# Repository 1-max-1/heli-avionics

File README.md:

# heli-avionics
This repository contains the electronics and software for a rc-helicopter control system. This includes an onboard flight computer and a mobile application for remote control.
The PCB is designed to drive coaxial blades using brushed DC motors. It also contains an rf transciever chip for wireless communication and a pressure sensor for altitude measurement.

I had to learn alot for this project, as there were several things I had no experience with such as the radio transceiver circuitry. In the end, it turned out well and was very fun to make.

# PCBWay
The PCB fabrication and assembly was sponsored by [PCBWay](https://www.pcbway.com/). I’m pleased with how it turned out, and I’ve written a short review below based on my experience working with them.

#### PCB Quality
The boards appear durable and well-made, with solid electrical connectivity. Silkscreen print is sharp and the overall finish gives off a professional feel.

#### Assembly Quality
Assembly was just as good. All components were placed with precision and the soldering was clean. There were no bridges, no excess, and everything stayed neatly within the boundaries.

#### Communication & Support
Working with PCBWay was a smooth experience. They were professional and quick to respond to any questions I had. One thing I really appreciated was their communication before making any key decisions. For example:
- When a part was unavailable, they suggested alternatives instead of just swapping it.
- They double-checked with me before sourcing alternative components.
- After assembly, the team contacted me about the orientation of a particular component as the markings were slightly ambiguous.

#### Pricing & Turnaround
Pricing was fair, considering the quality and the support included. Quoting and sourcing components was made easy — PCBWay handled that for me, which saved a lot of time. Shipping was fast and the boards arrived well-packed.

Overall, I'm happy with the result and wouldn’t hesitate to use PCBWay again in future projects. If you’re looking for a PCB manufacturer that’s reliable, responsive, and produces high-quality results, they’re worth checking out.

# Electronics
**Motor drivers**

The system uses three `DRV8212` BDC motor drivers to drive the tail and coaxial propellors. Some analysis shows that these chips should handle the current demands while remaining below maximum safe temperatures.
The motor driver circuit also includes significant bulk capacitance to handle large spikes in motor current.

The first design of the motor driver circuit used 1 driver chip for both motors. However after more testing, I found that the motors drew more current than expected when at full power. This was over the maximum limit of the motor driver chip. Initially, I started looking for replacement chips with better capabilities. However, the options were either too big, unavailable or could not operate at the voltage I wanted. Eventually, I realised this was the wrong way to go about it and decided to have another look at the original drivers. I discovered that if the 2 outputs on the chip were joined together, this would effectively double the maximum current, which was now sufficient for these motors. However, this solution does require 2 driver chips instead of one. I initially had concerns about space on the board, but after many hours of rearranging and rerouting I found a way to fit both parts on the board.

**MCU**

The MCU is an `atmega4808`. Although possibly not the fanciest choice, I selected this one because it's easy to program, I have used it before, and I know how to make it work.

**Programming**

The MCU can be programmed through UPDI or through the USART pins (once the bootloader has been uploaded). These are broken out to pin headers for easy access. The board also includes an external reset line + button.

I have also broken out an I2C line and a spare GPIO to another pin header in case I want to add more things onto the helicopter in the future.

**Radio**

This board includes a rf transceiver: `nrf24l01`. Like the MCU, this is not fancy but there's alot of documentation for it and I'd rather start with something easier because my rf knowledge is limited (for now).
The board contains an impedance matching network to match the transceiver output to 50 ohms. A wire antenna is used because it should give the best range and I dont have space for a PCB antenna or any bulky connectors like SMA. The antenna will also have to be tuned by cutting it to a specific length. I think UC has network analyzers which could help with this...

**Power regulation**

There are two seperate `TPS7A2030` voltage regulators - one for the radio and one for the rest of the circuit. This is done to try and minimize noise on the radio. The MCU also keeps track of the battery voltage through a divider to ensure that it remains at a safe level.

**Sensors**

The board includes a `BMP390` pressure sensor which can be used to determine the altitude of the helicopter.

# Software
TODO

Using platformIO, c++

### AeroLink
IN PROGRESS

This is a small esp32-based device which is placed near the user when flying the helicopter.
It acts as a bridge between the flight computer and the mobile application.
BLE messages are processed and sent over a long range nrf24 link, and vice versa.

# Controller app
IN PROGRESS

This is a [React Native](https://reactnative.dev/) mobile application for control of the helicopter.
It includes throttle and directional controls, trim adjustment, buttons for extra features (e.g. auto landing), telemetry display and signal strength indication.
The app automatically connects to the AeroLink and communicates with it.

# Why?
I found this helicopter in an e-waste center. The remote was missing and some of the electronics seemed to be burnt. 

|  | 
|:--:| 
| *Disassembled helicopter on test stand* |

After taking it apart and relubricating all the shafts and gears, I tested the motors and they still seemed to work fine.
I decided it would be fun to fix it up and make my own controller for it.

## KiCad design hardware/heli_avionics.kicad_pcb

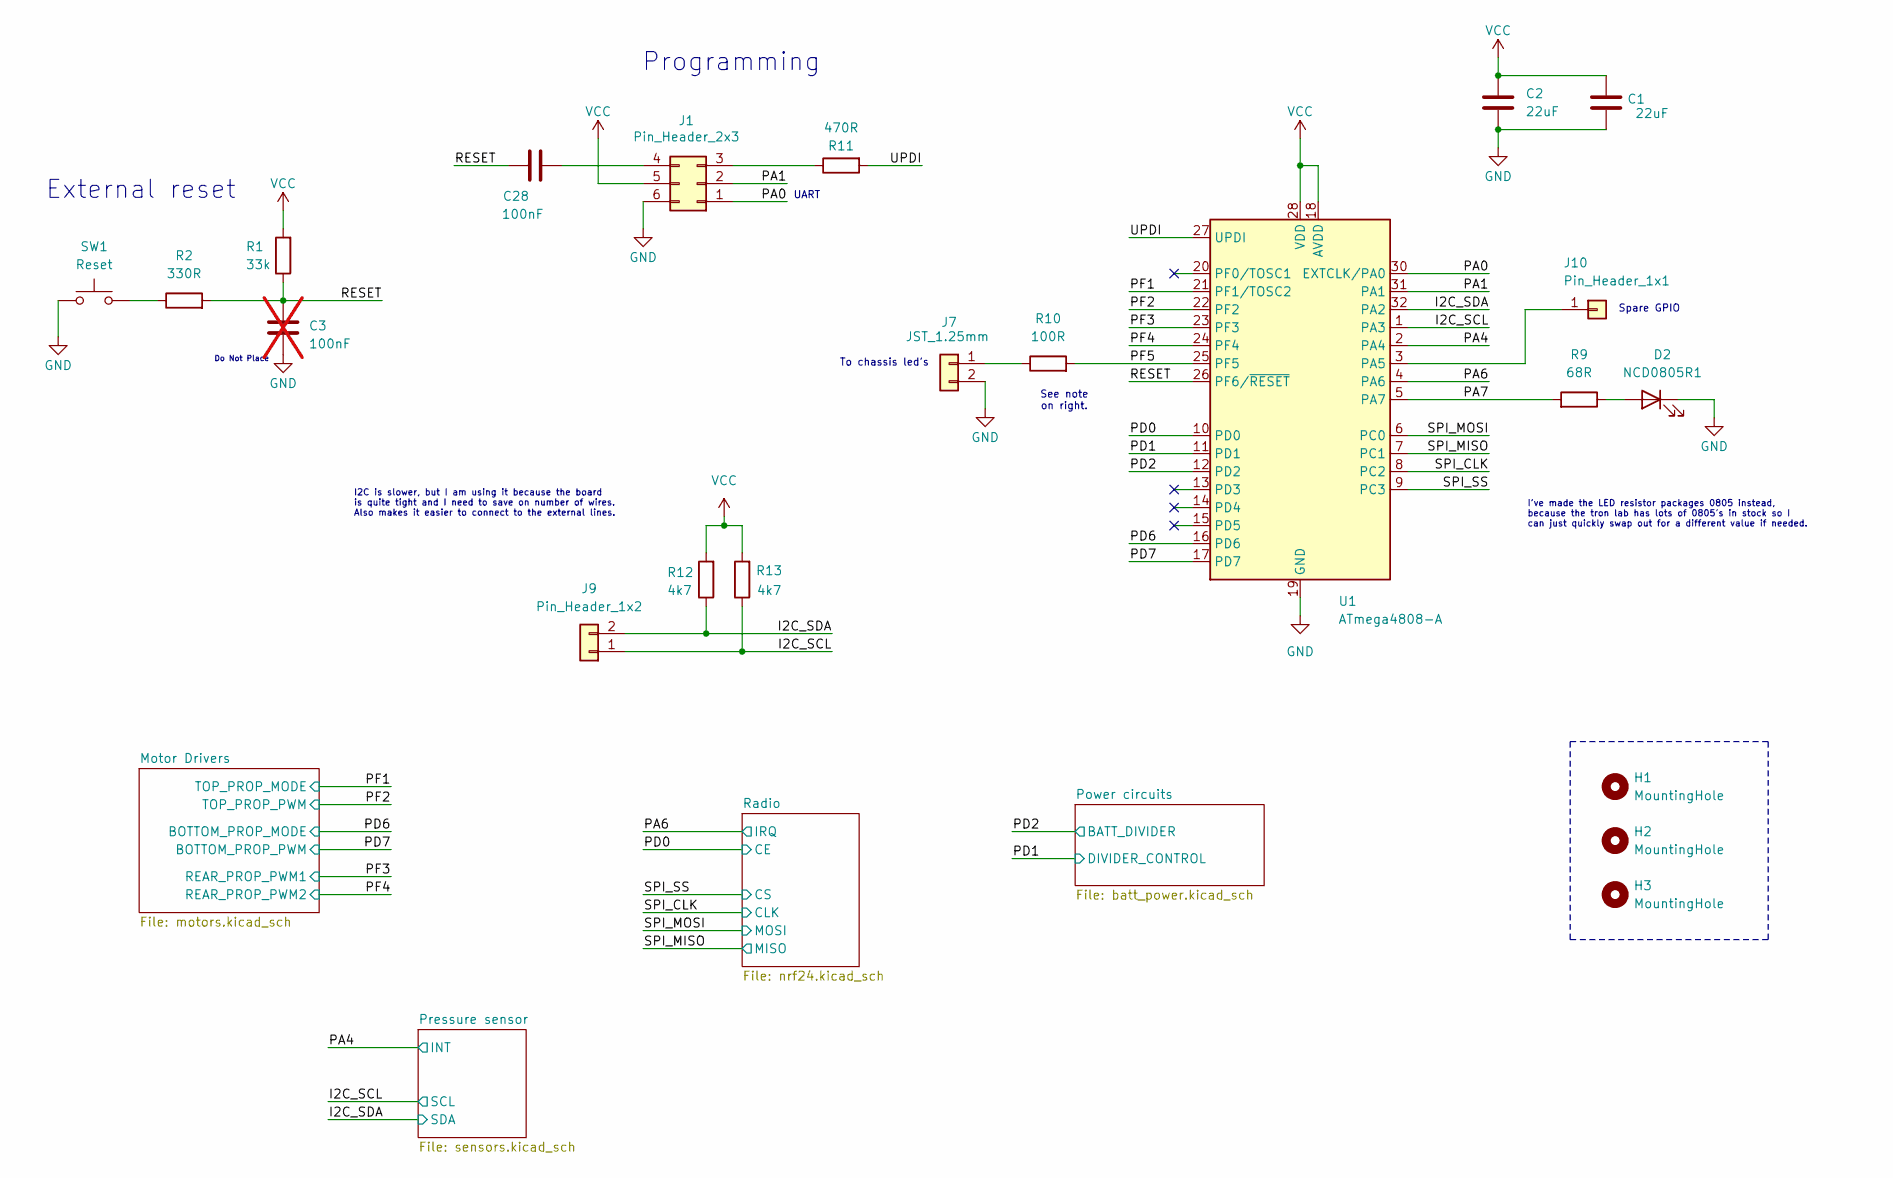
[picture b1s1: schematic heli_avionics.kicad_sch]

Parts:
C1, C2: 22uF; C_0603_1608Metric_Pad1.08x0.95mm_HandSolder; MPN CL10A226MQ8NRNC; LCSC Part # C59461
C3: 100nF; C_0603_1608Metric_Pad1.08x0.95mm_HandSolder; MPN CC0603KRX7R9BB104; LCSC Part # C14663; not fitted
C28: 100nF; C_0603_1608Metric_Pad1.08x0.95mm_HandSolder; MPN CC0603KRX7R9BB104; LCSC Part # C14663
D2: NCD0805R1; LED_0805_2012Metric_Pad1.15x1.40mm_HandSolder; MPN NCD0805R1; LCSC Part # C84256
H1, H2, H3: MountingHole; MountingHole_2mm
J1: Pin_Header_2x3; PinHeader_2x03_P2.54mm_Vertical
J7: JST_1.25mm; Molex_PicoBlade_53047-0210_1x02_P1.25mm_Vertical
J9: Pin_Header_1x2; PinHeader_1x02_P2.54mm_Vertical
J10: Pin_Header_1x1; PinHeader_1x01_P2.54mm_Vertical
R1: 33k; R_0603_1608Metric_Pad0.98x0.95mm_HandSolder; MPN 0603WAF3302T5E; LCSC Part # C4216
R2: 330R; R_0603_1608Metric_Pad0.98x0.95mm_HandSolder; MPN 0603WAF3300T5E; LCSC Part # C23138
R9: 68R; R_0805_2012Metric_Pad1.20x1.40mm_HandSolder; MPN 0805W8F680JT5E; LCSC Part # C17802
R10: 100R; R_0805_2012Metric_Pad1.20x1.40mm_HandSolder; MPN 0805W8F1000T5E; LCSC Part # C17408
R11: 470R; R_0603_1608Metric_Pad0.98x0.95mm_HandSolder; MPN 0603WAF4700T5E; LCSC Part # C23179
R12, R13: 4k7; R_0603_1608Metric_Pad0.98x0.95mm_HandSolder; MPN 0603WAF4701T5E; LCSC Part # C23162
SW1: Reset; SW_Push_SPST_NO_Alps_SKRK; MPN SKRKAEE020; LCSC Part # C115357
U1: ATmega4808-A; TQFP-32_7x7mm_P0.8mm; MPN ATMEGA4808-AFR; LCSC Part # C2052755

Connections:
/I2C_SCL: J9.1, R13.1, U1.1 (PA3); also elsewhere on the board
/I2C_SDA: J9.2, R12.1, U1.32 (PA2); also elsewhere on the board
/PA0: J1.1, U1.30 (EXTCLK/PA0)
/PA1: J1.2, U1.31 (PA1)
/PA4: U1.2 (PA4); also elsewhere on the board
/PA6: U1.4 (PA6); also elsewhere on the board
/PA7: R9.2, U1.5 (PA7)
/PD0: U1.10 (PD0); also elsewhere on the board
/PD1: U1.11 (PD1); also elsewhere on the board
/PD2: U1.12 (PD2); also elsewhere on the board
/PD6: U1.16 (PD6); also elsewhere on the board
/PD7: U1.17 (PD7); also elsewhere on the board
/PF1: U1.21 (PF1/TOSC2); also elsewhere on the board
/PF2: U1.22 (PF2); also elsewhere on the board
/PF3: U1.23 (PF3); also elsewhere on the board
/PF4: U1.24 (PF4); also elsewhere on the board
/PF5: R10.2, U1.25 (PF5)
/RESET: C3.1, C28.1, R1.1, R2.2, U1.26 (PF6/~RESET)
/SPI_CLK: U1.8 (PC2); also elsewhere on the board
/SPI_MISO: U1.7 (PC1); also elsewhere on the board
/SPI_MOSI: U1.6 (PC0); also elsewhere on the board
/SPI_SS: U1.9 (PC3); also elsewhere on the board
/UPDI: R11.2, U1.27 (UPDI)
GND: C1.2, C2.2, C3.2, D2.1 (K), J1.6, J7.2, SW1.1, U1.19 (GND), U1.29 (GND); also elsewhere on the board
unnamed: D2.2 (A), R9.1
unnamed: J1.3, R11.1
unnamed: C28.2, J1.4
unnamed: J7.1, R10.1
unnamed: J10.1, U1.3 (PA5)
unnamed: R2.1, SW1.2
VCC: C1.1, C2.1, J1.5, R1.2, R12.2, R13.2, U1.18 (AVDD), U1.28 (VDD); also elsewhere on the board

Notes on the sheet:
Do Not Place
I've made the LED resistor packages 0805 instead, because the tron lab has lots of 0805's in stock so I can just quickly swap out for a different value if needed.
I2C is slower, but I am using it because the board is quite tight and I need to save on number of wires. Also makes it easier to connect to the external lines.
UART
See note on right.
To chassis led's
Spare GPIO
Programming
External reset

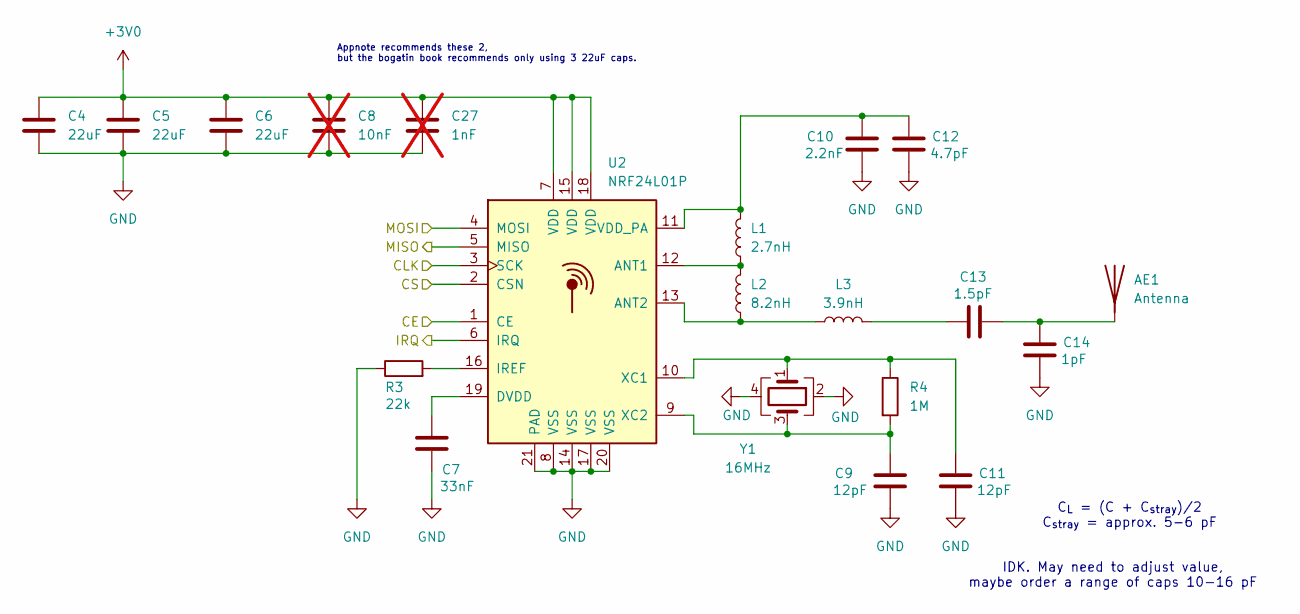
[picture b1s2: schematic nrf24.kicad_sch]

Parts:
AE1: Antenna; SolderWire-0.5sqmm_1x01_D0.9mm_OD2.1mm
C4, C5, C6: 22uF; C_0603_1608Metric_Pad1.08x0.95mm_HandSolder; MPN CL10A226MQ8NRNC; LCSC Part # C59461
C7: 33nF; C_0603_1608Metric_Pad1.08x0.95mm_HandSolder; MPN CL10B333KB8NNNC; LCSC Part # C21117
C8: 10nF; C_0603_1608Metric_Pad1.08x0.95mm_HandSolder; MPN 0603B103K500NT; LCSC Part # C57112; not fitted
C9, C11: 12pF; C_0603_1608Metric_Pad1.08x0.95mm_HandSolder; MPN CC0603FRNPO9BN120; LCSC Part # C519482
C10: 2.2nF; C_0603_1608Metric_Pad1.08x0.95mm_HandSolder; MPN 0603B222K500NT; LCSC Part # C1604
C12: 4.7pF; C_0603_1608Metric_Pad1.08x0.95mm_HandSolder; MPN 0603CG4R7C500NT; LCSC Part # C1669
C13: 1.5pF; C_0603_1608Metric_Pad1.08x0.95mm_HandSolder; MPN HH18N1R5B500CT
C14: 1pF; C_0603_1608Metric_Pad1.08x0.95mm_HandSolder; MPN HH18N1R0B500CT
C27: 1nF; C_0603_1608Metric_Pad1.08x0.95mm_HandSolder; MPN CL10B102KB8NNNC; LCSC Part # C1588; not fitted
L1: 2.7nH; L_0603_1608Metric_Pad1.05x0.95mm_HandSolder; MPN BSCQ000603032N7B00
L2: 8.2nH; L_0603_1608Metric_Pad1.05x0.95mm_HandSolder; MPN BSCQ000603038N2H00
L3: 3.9nH; L_0603_1608Metric_Pad1.05x0.95mm_HandSolder; MPN BSCQ000603033N9B00
R3: 22k; R_0603_1608Metric_Pad0.98x0.95mm_HandSolder; MPN 0603WAF2202T5E; LCSC Part # C31850
R4: 1M; R_0603_1608Metric_Pad0.98x0.95mm_HandSolder; MPN 0603WAF1004T5E; LCSC Part # C22935
U2: NRF24L01P; NRF24L01_HandSolder_SpecialPad; MPN NRF24L01P-R; LCSC Part # C8791
Y1: 16MHz; Crystal_SMD_3225-4Pin_3.2x2.5mm; MPN X322516MLB4SI; LCSC Part # C13738

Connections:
+3V0: C4.1, C5.1, C6.1, C8.1, C27.1, U2.7 (VDD), U2.15 (VDD), U2.18 (VDD); also elsewhere on the board
/PA6: U2.6 (IRQ); also elsewhere on the board
/PD0: U2.1 (CE); also elsewhere on the board
/SPI_CLK: U2.3 (SCK); also elsewhere on the board
/SPI_MISO: U2.5 (MISO); also elsewhere on the board
/SPI_MOSI: U2.4 (MOSI); also elsewhere on the board
/SPI_SS: U2.2 (CSN); also elsewhere on the board
GND: C4.2, C5.2, C6.2, C7.2, C8.2, C9.2, C10.2, C11.2, C12.2, C14.2, C27.2, R3.1, U2.8 (VSS), U2.14 (VSS), U2.17 (VSS), U2.20 (VSS), U2.21 (PAD), Y1.2, Y1.4; also elsewhere on the board
unnamed: AE1.1 (A), C13.2, C14.1
unnamed: C13.1, L3.2
unnamed: L1.1, L2.2, U2.12 (ANT1)
unnamed: L2.1, L3.1, U2.13 (ANT2)
unnamed: C7.1, U2.19 (DVDD)
unnamed: R3.2, U2.16 (IREF)
unnamed: C10.1, C12.1, L1.2, U2.11 (VDD_PA)
unnamed: C11.1, R4.1, U2.10 (XC1), Y1.1
unnamed: C9.1, R4.2, U2.9 (XC2), Y1.3

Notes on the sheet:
C_{L} = (C + C_{stray})/2 C_{stray} = approx. 5-6 pF
Appnote recommends these 2, but the bogatin book recommends only using 3 22uF caps.
IDK. May need to adjust value, maybe order a range of caps 10-16 pF

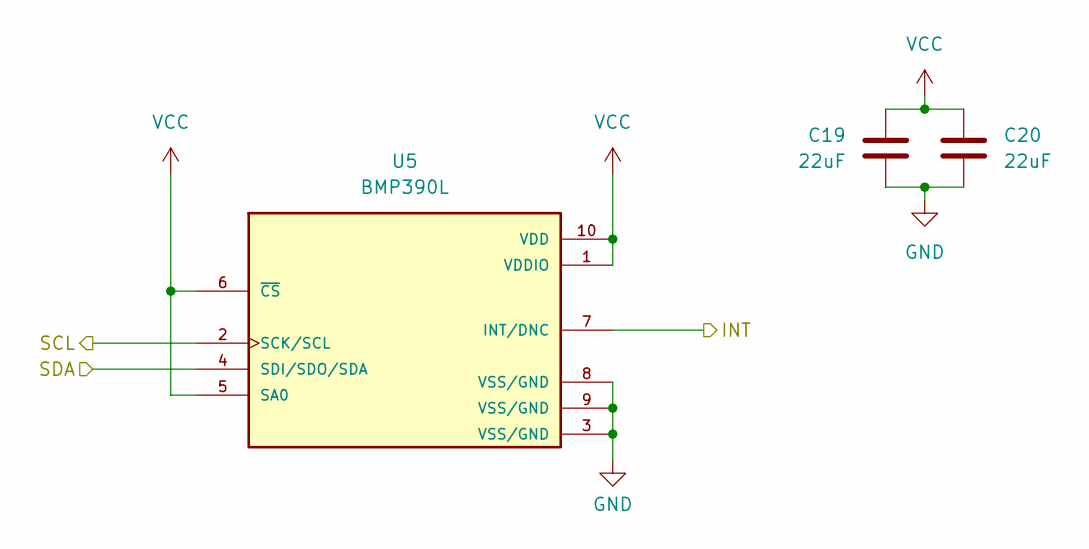
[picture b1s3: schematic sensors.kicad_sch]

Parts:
C19, C20: 22uF; C_0603_1608Metric_Pad1.08x0.95mm_HandSolder; MPN CL10A226MQ8NRNC; LCSC Part # C59461
U5: BMP390L; MPN BMP390L; LCSC Part # C2684802

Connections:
/I2C_SCL: U5.2 (SCK/SCL); also elsewhere on the board
/I2C_SDA: U5.4 (SDI/SDO/SDA); also elsewhere on the board
/PA4: U5.7 (INT/DNC); also elsewhere on the board
GND: C19.2, C20.2, U5.3 (VSS/GND), U5.8 (VSS/GND), U5.9 (VSS/GND); also elsewhere on the board
VCC: C19.1, C20.1, U5.1 (VDDIO), U5.5 (SA0), U5.6 (~CS), U5.10 (VDD); also elsewhere on the board

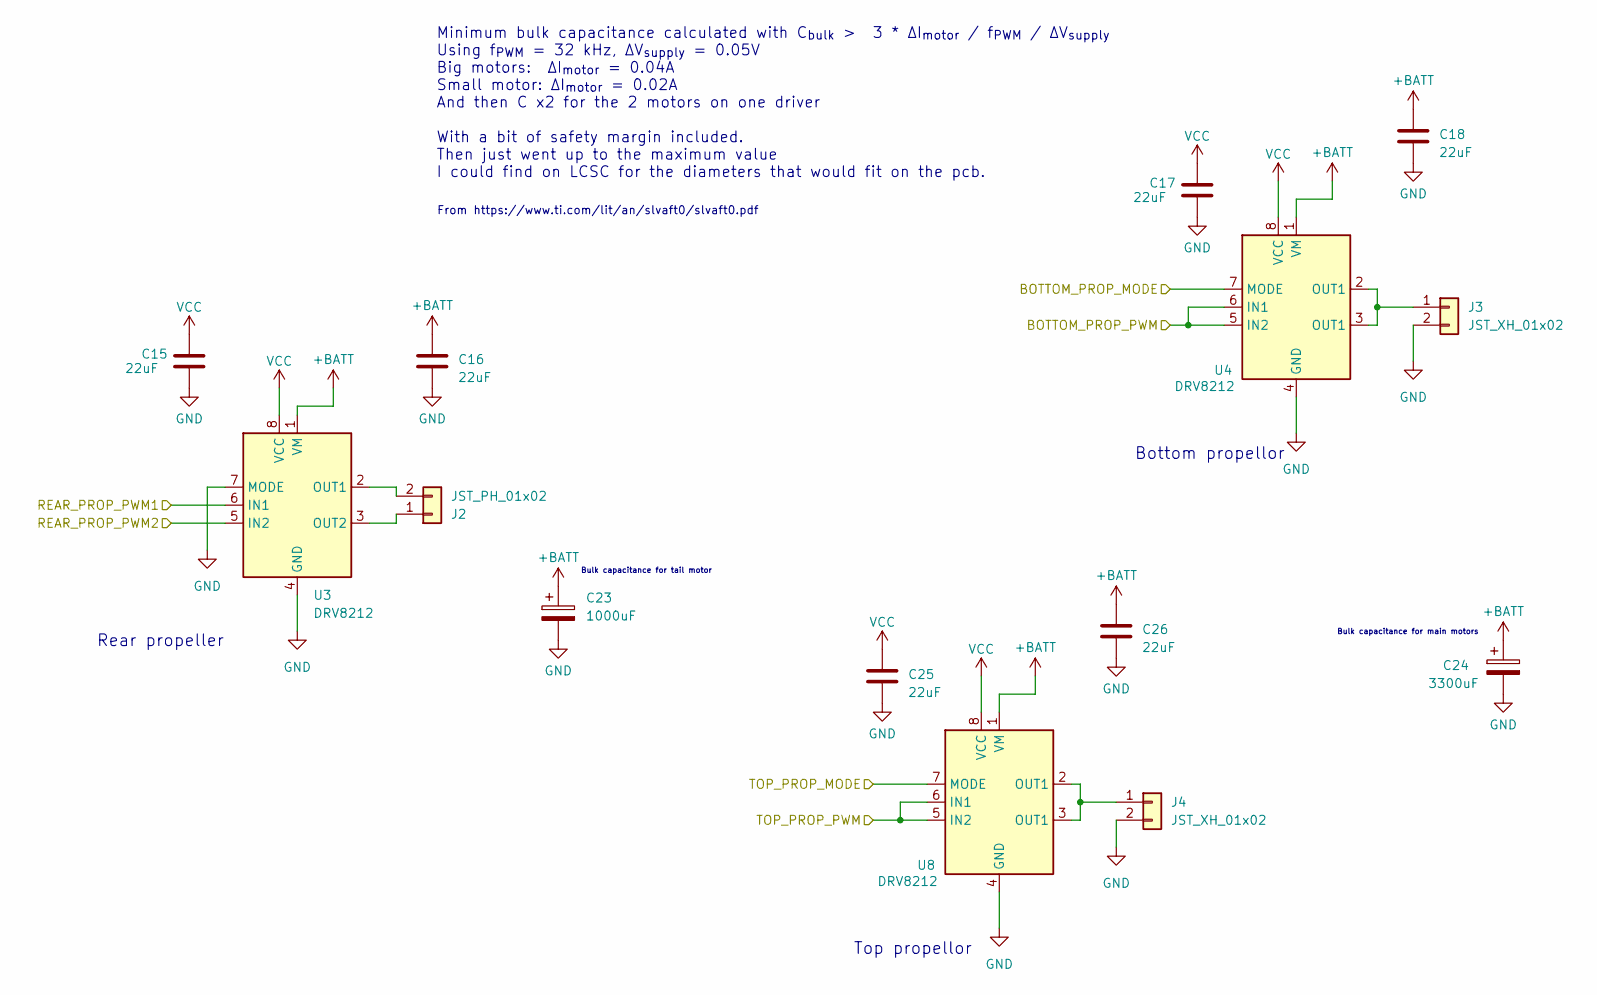
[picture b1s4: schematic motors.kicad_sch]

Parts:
C15, C16, C17, C18, C25, C26: 22uF; C_0603_1608Metric_Pad1.08x0.95mm_HandSolder; MPN CL10A226MQ8NRNC; LCSC Part # C59461
C23: 1000uF; CP_Radial_D6.3mm_P2.50mm; MPN SPT1AM102E14ORVZC; LCSC Part # C3024245
C24: 3300uF; CP_Radial_D10.0mm_P5.00mm; MPN RL1A332MG250A00CE0; LCSC Part # C240437
J2: JST_PH_01x02; JST_PH_B2B-PH-K_1x02_P2.00mm_Vertical
J3, J4: JST_XH_01x02; JST_XH_B2B-XH-A_1x02_P2.50mm_Vertical
U3, U4, U8: DRV8212; WSON-8-1EP_2x2mm_P0.5mm_EP0.9x1.6mm_ThermalVias; MPN DRV8212DSGR; LCSC Part # C2843766

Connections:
+BATT: C16.1, C18.1, C23.1, C24.1, C26.1, U3.1 (VM), U4.1 (VM), U8.1 (VM); also elsewhere on the board
/PD6: U4.7 (MODE); also elsewhere on the board
/PD7: U4.5 (IN2), U4.6 (IN1); also elsewhere on the board
/PF1: U8.7 (MODE); also elsewhere on the board
/PF2: U8.5 (IN2), U8.6 (IN1); also elsewhere on the board
/PF3: U3.6 (IN1); also elsewhere on the board
/PF4: U3.5 (IN2); also elsewhere on the board
GND: C15.2, C16.2, C17.2, C18.2, C23.2, C24.2, C25.2, C26.2, J3.2, J4.2, U3.4 (GND), U3.7 (MODE), U3.9 (GND), U4.4 (GND), U4.9 (GND), U8.4 (GND), U8.9 (GND); also elsewhere on the board
unnamed: J2.1, U3.3 (OUT2)
unnamed: J2.2, U3.2 (OUT1)
unnamed: J3.1, U4.2 (OUT1), U4.3 (OUT1)
unnamed: J4.1, U8.2 (OUT1), U8.3 (OUT1)
VCC: C15.1, C17.1, C25.1, U3.8 (VCC), U4.8 (VCC), U8.8 (VCC); also elsewhere on the board

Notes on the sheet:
Top propellor
Rear propeller
Minimum bulk capacitance calculated with C_{bulk} > 3 * ∆I_{motor} / f_{PWM} / ∆V_{supply} Using f_{PWM} = 32 kHz, ∆V_{supply} = 0.05V Big motors: ∆I_{motor} = 0.04A Small motor: ∆I_{motor} = 0.02A And then C x2 for the 2 motors on one driver With a bit of safety margin included. Then just went up 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
From https://www.ti.com/lit/an/slvaft0/slvaft0.pdf
Bulk capacitance for tail motor
Bottom propellor
Bulk capacitance for main motors

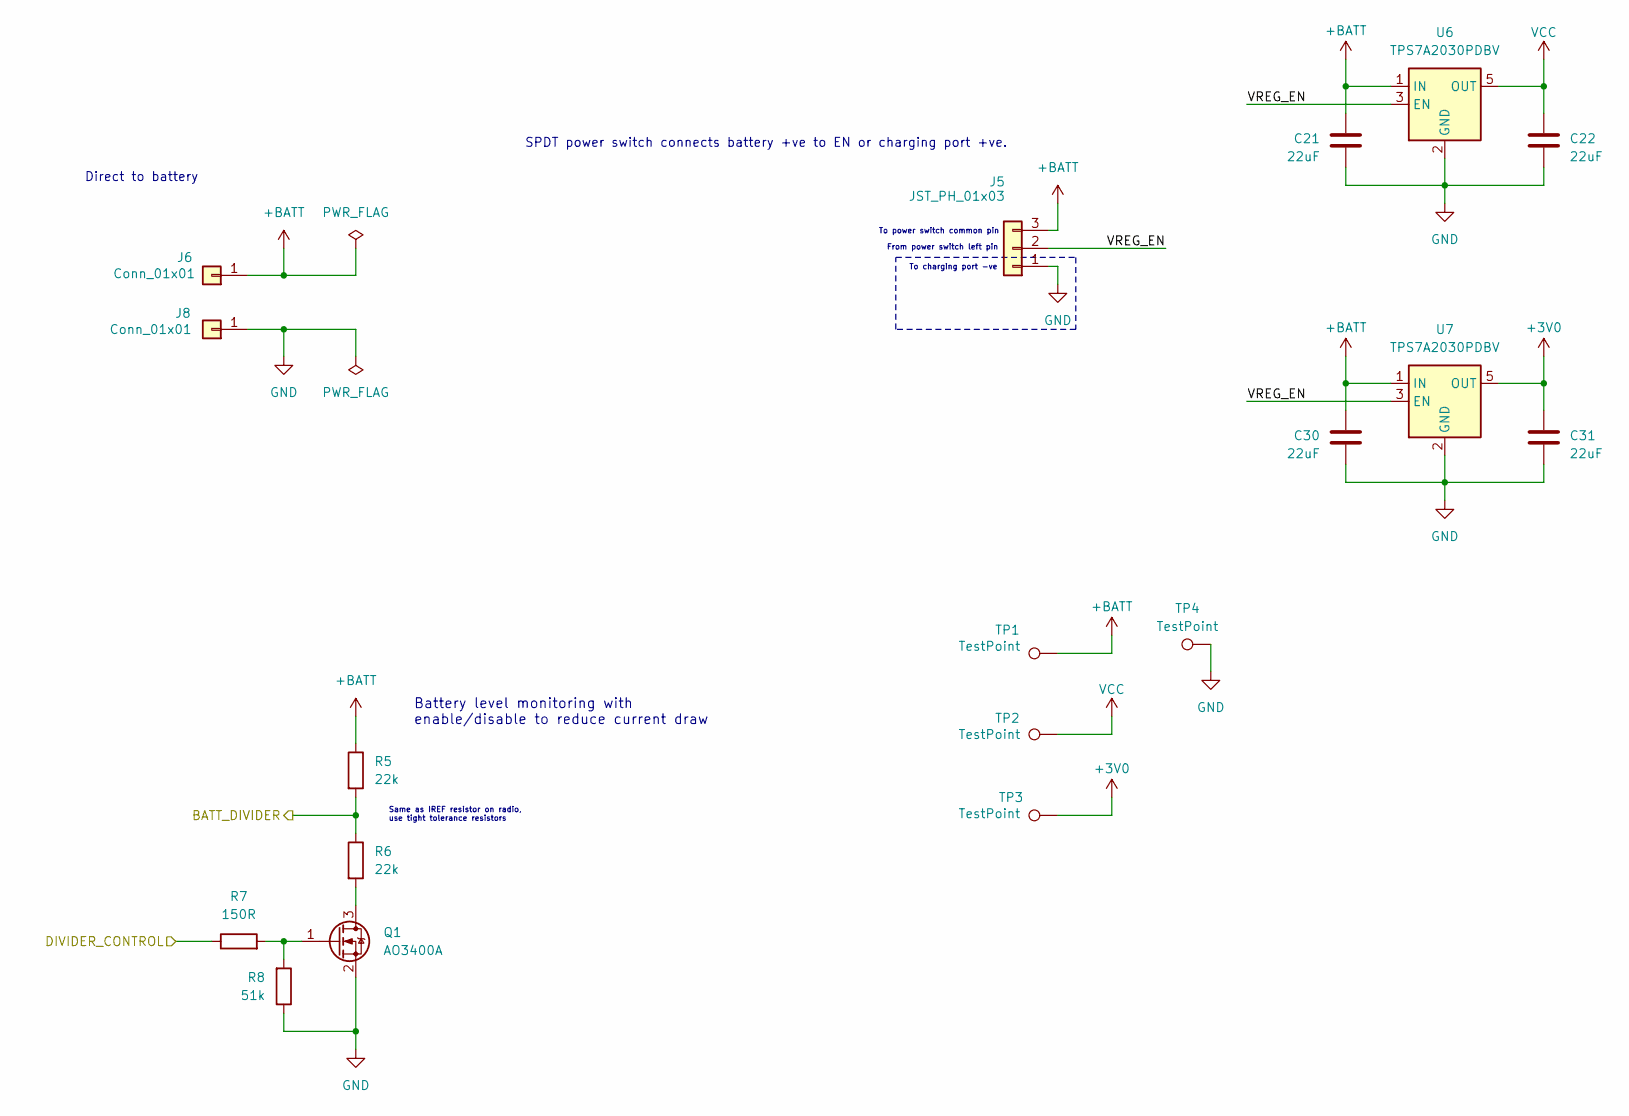
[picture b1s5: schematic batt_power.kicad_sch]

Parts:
C21, C22, C30, C31: 22uF; C_0603_1608Metric_Pad1.08x0.95mm_HandSolder; MPN CL10A226MQ8NRNC; LCSC Part # C59461
J5: JST_PH_01x03; JST_PH_B3B-PH-K_1x03_P2.00mm_Vertical
J6, J8: Conn_01x01; SolderWire-1sqmm_1x01_D1.4mm_OD3.9mm
Q1: AO3400A; SOT-23; MPN AO3400A; LCSC Part # C20917
R5, R6: 22k; R_0603_1608Metric_Pad0.98x0.95mm_HandSolder; MPN 0603WAF2202T5E; LCSC Part # C31850
R7: 150R; R_0603_1608Metric_Pad0.98x0.95mm_HandSolder; MPN 0603WAF1500T5E; LCSC Part # C22808
R8: 51k; R_0603_1608Metric_Pad0.98x0.95mm_HandSolder; MPN 0603WAF5102T5E; LCSC Part # C23196
TP1, TP3: TestPoint; TestPoint_Pad_1.5x1.5mm
TP2, TP4: TestPoint; TestPoint_Pad_D1.5mm
U6, U7: TPS7A2030PDBV; SOT-23-5_HandSoldering; MPN TPS7A2030PDBVR; LCSC Part # C963429

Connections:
+3V0: C31.1, TP3.1, U7.5 (OUT); also elsewhere on the board
+BATT: C21.1, C30.1, J5.3, J6.1, R5.1, TP1.1, U6.1 (IN), U7.1 (IN); also elsewhere on the board
/PD1: R7.1; also elsewhere on the board
/PD2: R5.2, R6.1; also elsewhere on the board
/Power circuits/VREG_EN: J5.2, U6.3 (EN), U7.3 (EN)
GND: C21.2, C22.2, C30.2, C31.2, J5.1, J8.1, Q1.2 (S), R8.1, TP4.1, U6.2 (GND), U7.2 (GND); also elsewhere on the board
unnamed: Q1.3 (D), R6.2
unnamed: Q1.1 (G), R7.2, R8.2
VCC: C22.1, TP2.1, U6.5 (OUT); also elsewhere on the board

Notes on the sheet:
To charging port -ve
Direct to battery
From power switch left pin
Same as IREF resistor on radio, use tight tolerance resistors
Battery level monitoring with enable/disable to reduce current draw
To power switch common pin
SPDT power switch connects battery +ve to EN or charging port +ve.

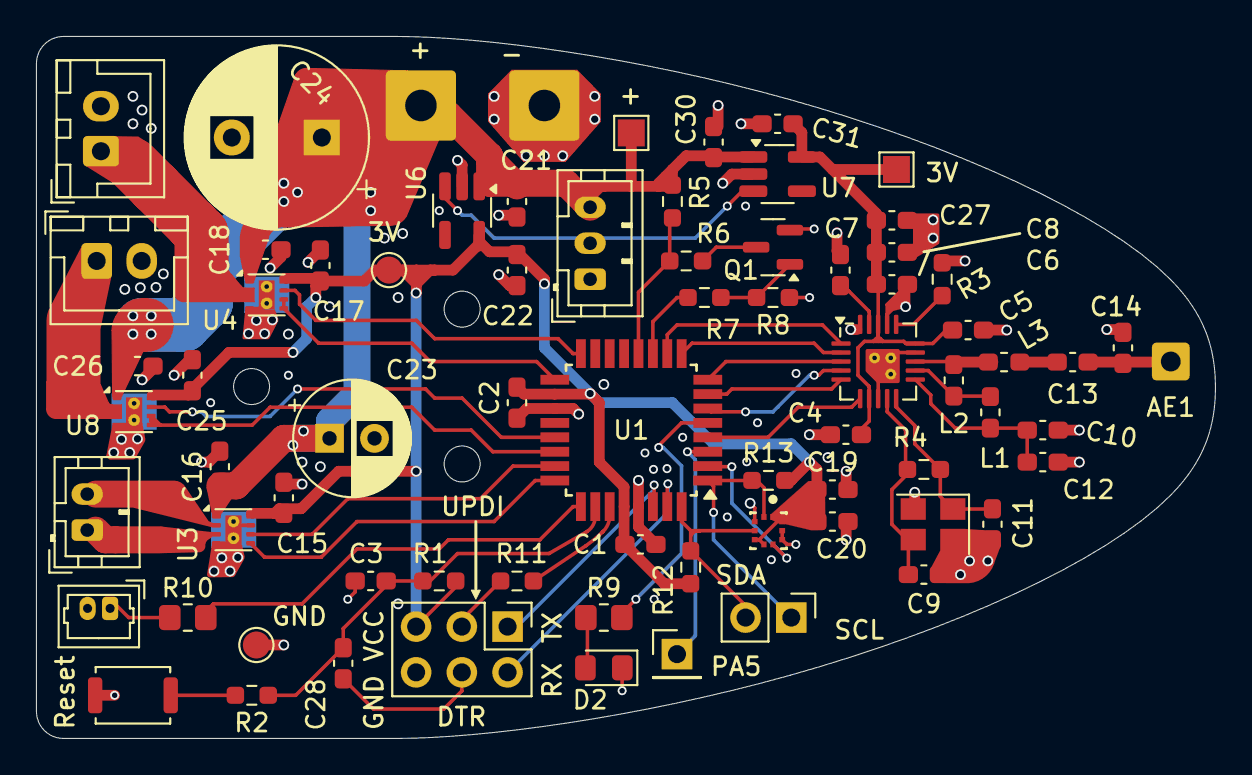
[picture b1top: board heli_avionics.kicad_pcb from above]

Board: 4 copper layers, 65.5 x 39.0 mm, 76 parts (0 on the bottom side), 49 nets.

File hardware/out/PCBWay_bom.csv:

Designator,Quantity,Value,Footprint,Package,MPN,DNP,Mount_Type,Description,LCSC Part #
"C1, C15, C16, C17, C18, C19, C2, C20, C21, C22, C25, C26, C30, C31, C4, C5, C6",17,22uF,C_0603_1608Metric_Pad1.08x0.95mm_HandSolder,,CL10A226MQ8NRNC,,smt,6.3V 22uF X5R ±20% 0603 Multilayer Ceramic Capacitors MLCC - SMD/SMT ROHS,C59461
C10,1,2.2nF,C_0603_1608Metric_Pad1.08x0.95mm_HandSolder,,0603B222K500NT,,smt,50V 2.2nF X7R ±10% 0603 Multilayer Ceramic Capacitors MLCC - SMD/SMT ROHS,C1604
"C11, C9",2,12pF,C_0603_1608Metric_Pad1.08x0.95mm_HandSolder,,CC0603FRNPO9BN120,,smt,50V 12pF NP0 ±1% 0603 Multilayer Ceramic Capacitors MLCC - SMD/SMT ROHS,C519482
C12,1,4.7pF,C_0603_1608Metric_Pad1.08x0.95mm_HandSolder,,0603CG4R7C500NT,,smt,50V 4.7pF C0G 0603 Multilayer Ceramic Capacitors MLCC - SMD/SMT ROHS,C1669
C13,1,1.5pF,C_0603_1608Metric_Pad1.08x0.95mm_HandSolder,,HH18N1R5B500CT,,smt,"1.5 pF ±0.1pF 50V Ceramic Capacitor C0G, NP0 0603 (1608 Metric)",
C14,1,1pF,C_0603_1608Metric_Pad1.08x0.95mm_HandSolder,,HH18N1R0B500CT,,smt,"1 pF ±0.1pF 50V Ceramic Capacitor C0G, NP0 0603 (1608 Metric)",
C27,1,1nF,C_0603_1608Metric_Pad1.08x0.95mm_HandSolder,,CL10B102KB8NNNC,Yes,smt,50V 1nF X7R ±10% 0603 Multilayer Ceramic Capacitors MLCC - SMD/SMT ROHS,C1588
C28,1,100nF,C_0603_1608Metric_Pad1.08x0.95mm_HandSolder,,CC0603KRX7R9BB104,,smt,50V 100nF X7R ±10% 0603 Multilayer Ceramic Capacitors MLCC - SMD/SMT ROHS,C14663
C3,1,100nF,C_0603_1608Metric_Pad1.08x0.95mm_HandSolder,,CC0603KRX7R9BB104,Yes,smt,50V 100nF X7R ±10% 0603 Multilayer Ceramic Capacitors MLCC - SMD/SMT ROHS,C14663
C7,1,33nF,C_0603_1608Metric_Pad1.08x0.95mm_HandSolder,,CL10B333KB8NNNC,,smt,50V 33nF X7R ±10% 0603 Multilayer Ceramic Capacitors MLCC - SMD/SMT ROHS,C21117
C8,1,10nF,C_0603_1608Metric_Pad1.08x0.95mm_HandSolder,,0603B103K500NT,Yes,smt,Unpolarized capacitor,C57112
D2,1,NCD0805R1,LED_0805_2012Metric_Pad1.15x1.40mm_HandSolder,,NCD0805R1,,smt,Red 25mA 67mcd~195mcd -30℃~+85℃ 615nm~630nm Independent Diode Red 130° 65mW 1.6V~2.6V 0805 LED Indication - Discrete ROHS,C84256
L1,1,2.7nH,L_0603_1608Metric_Pad1.05x0.95mm_HandSolder,,BSCQ000603032N7B00,,smt,2.7 nH Unshielded Multilayer Inductor 400 mA 320mOhm Max 0201 (0603 Metric),
L2,1,8.2nH,L_0603_1608Metric_Pad1.05x0.95mm_HandSolder,,BSCQ000603038N2H00,,smt,8.2 nH Unshielded Multilayer Inductor 290 mA 570mOhm Max 0201 (0603 Metric),
L3,1,3.9nH,L_0603_1608Metric_Pad1.05x0.95mm_HandSolder,,BSCQ000603033N9B00,,smt,3.9 nH Unshielded Multilayer Inductor 350 mA 410mOhm Max 0201 (0603 Metric),
Q1,1,AO3400A,SOT-23,,AO3400A,,smt,"30V Vds, 5.7A Id, N-Channel MOSFET, SOT-23",C20917
R1,1,33k,R_0603_1608Metric_Pad0.98x0.95mm_HandSolder,,0603WAF3302T5E,,smt,100mW Thick Film Resistors 75V ±100ppm/℃ ±1% 33kΩ 0603 Chip Resistor - Surface Mount ROHS,C4216
R10,1,100R,R_0805_2012Metric_Pad1.20x1.40mm_HandSolder,,0805W8F1000T5E,,smt,125mW Thick Film Resistors 150V ±100ppm/℃ ±1% 100Ω 0805 Chip Resistor - Surface Mount ROHS,C17408
R11,1,470R,R_0603_1608Metric_Pad0.98x0.95mm_HandSolder,,0603WAF4700T5E,,smt,100mW Thick Film Resistors 75V ±100ppm/℃ ±1% 470Ω 0603 Chip Resistor - Surface Mount ROHS,C23179
"R12, R13",2,4k7,R_0603_1608Metric_Pad0.98x0.95mm_HandSolder,,0603WAF4701T5E,,smt,100mW Thick Film Resistors 75V ±100ppm/℃ ±1% 4.7kΩ 0603 Chip Resistor - Surface Mount ROHS,C23162
R2,1,330R,R_0603_1608Metric_Pad0.98x0.95mm_HandSolder,,0603WAF3300T5E,,smt,100mW Thick Film Resistors 75V ±100ppm/℃ ±1% 330Ω 0603 Chip Resistor - Surface Mount ROHS,C23138
"R3, R5, R6",3,22k,R_0603_1608Metric_Pad0.98x0.95mm_HandSolder,,0603WAF2202T5E,,smt,100mW Thick Film Resistors 75V ±100ppm/℃ ±1% 22kΩ 0603 Chip Resistor - Surface Mount ROHS,C31850
R4,1,1M,R_0603_1608Metric_Pad0.98x0.95mm_HandSolder,,0603WAF1004T5E,,smt,100mW Thick Film Resistors 75V ±100ppm/℃ ±1% 1MΩ 0603 Chip Resistor - Surface Mount ROHS,C22935
R7,1,150R,R_0603_1608Metric_Pad0.98x0.95mm_HandSolder,,0603WAF1500T5E,,smt,100mW Thick Film Resistors 75V ±100ppm/℃ ±1% 150Ω 0603 Chip Resistor - Surface Mount ROHS,C22808
R8,1,51k,R_0603_1608Metric_Pad0.98x0.95mm_HandSolder,,0603WAF5102T5E,,smt,100mW Thick Film Resistors 75V ±100ppm/℃ ±1% 51kΩ 0603 Chip Resistor - Surface Mount ROHS,C23196
R9,1,68R,R_0805_2012Metric_Pad1.20x1.40mm_HandSolder,,0805W8F680JT5E,,smt,125mW Thick Film Resistors 150V ±1% ±200ppm/℃ 68Ω 0805 Chip Resistor - Surface Mount ROHS,C17802
SW1,1,Reset,SW_Push_SPST_NO_Alps_SKRK,,SKRKAEE020,,smt,2.9mm 2mm Round Button 50mA Vertical welding 3.9mm SPST 12V SMD Tactile Switches ROHS,C115357
U1,1,ATmega4808-A,TQFP-32_7x7mm_P0.8mm,,ATMEGA4808-AFR,,smt,"AVR Microcontroller, 20MHz, 48kB Flash, 6kB SRAM, 256B EEPROM, TQFP-32",C2052755
U2,1,NRF24L01P,QFN-20-1EP_4x4mm_P0.5mm_EP2.5x2.5mm,,NRF24L01P-R,,smt,"Ultra low power 2 Mbps 2.4GHz RF Transceiver, QFN-20",C8791
"U3, U4, U8",3,DRV8212,WSON-8-1EP_2x2mm_P0.5mm_EP0.9x1.6mm_ThermalVias,,DRV8212DSGR,,smt,"H-Bridge driver, 4A, Low Voltage, PWM input, Half Bridge Mode, Low-Power Sleep Mode, WSON-8",C2843766
U5,1,BMP390L,BMP390L LGA 2.0x2.0 mm,,BMP390L,,smt,"24-bit barometric pressure sensor, low-noise, low-power.",C2684802
"U6, U7",2,TPS7A2030PDBV,SOT-23-5_HandSoldering,,TPS7A2030PDBVR,,smt,"300-mA Ultra-Low-Noise Low-IQ, High PSRR LDO, 3.0V, SOT-23",C963429
Y1,1,16MHz,Crystal_SMD_3225-4Pin_3.2x2.5mm,,X322516MLB4SI,,smt,"Four pin crystal, 16MHz, X322516MLB4SI",C13738

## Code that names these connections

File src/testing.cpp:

#include <Arduino.h>
#include <Wire.h>
#include <SPI.h>
#include <Adafruit_Sensor.h>
#include <Adafruit_BMP3XX.h>
#include <RF24.h>
#include <printf.h>

namespace {

#define SEALEVELPRESSURE_HPA (1033)

Adafruit_BMP3XX bmp;

#define BATT_DIVIDER_EN PIN_PD1
#define BATT_DIVIDER PIN_PD2

#define TOP_PROP_MODE PIN_PF1
#define TOP_PROP_PWM PIN_PF2
#define BOTTOM_PROP_MODE PIN_PD6
#define BOTTOM_PROP_PWM PIN_PD7
#define REAR_PROP_PWM1 PIN_PF3
#define REAR_PROP_PWM2 PIN_PF4

#define NRF24_CE PIN_PD0
#define NRF24_CS PIN_PC3
RF24 radio(NRF24_CE, NRF24_CS);

const byte* txAddress = (const byte*)"aviTX";
const byte* rxAddress = (const byte*)"aviRX";

void setupMotorDrivers();

void tailMotor(uint8_t val, bool forward) {
	register8_t& compareRegister = forward ? TCA0.SPLIT.HCMP0 : TCA0.SPLIT.HCMP1;
	register8_t& otherRegister = !forward ? TCA0.SPLIT.HCMP0 : TCA0.SPLIT.HCMP1;
	otherRegister = 0;
	compareRegister = val;
}

void topMotor(uint8_t val) {
	TCA0.SPLIT.LCMP2 = val;
}

void bottomMotor(uint8_t val) {
	TCA0.SPLIT.LCMP0 = val;
}

unsigned long timeOfLastSend = 0;

void setup() {
	pinMode(BATT_DIVIDER_EN, OUTPUT);
	digitalWrite(BATT_DIVIDER_EN, HIGH);
	delay(100);
	pinMode(BATT_DIVIDER, INPUT);

	Serial.begin(9600);
	printf_begin();

	pinMode(LED_BUILTIN, OUTPUT);
	digitalWrite(LED_BUILTIN, HIGH);

	if (!bmp.begin_I2C()) {
		Serial.println("Could not find a valid BMP3 sensor, check wiring!");
		while (1);
	}

	// Set up oversampling and filter initialization
	bmp.setTemperatureOversampling(BMP3_OVERSAMPLING_8X);
	bmp.setPressureOversampling(BMP3_OVERSAMPLING_4X);
	bmp.setIIRFilterCoeff(BMP3_IIR_FILTER_COEFF_3);
	bmp.setOutputDataRate(BMP3_ODR_50_HZ);

	pinMode(TOP_PROP_MODE, INPUT);
	pinMode(TOP_PROP_PWM, OUTPUT);
	pinMode(BOTTOM_PROP_MODE, INPUT);
	pinMode(BOTTOM_PROP_PWM, OUTPUT);
	pinMode(REAR_PROP_PWM1, OUTPUT);
	pinMode(REAR_PROP_PWM2, OUTPUT);
	pinMode(PIN_PF0, OUTPUT);

	setupMotorDrivers();

	// Bring motor drivers out of sleep mode
	digitalWriteFast(REAR_PROP_PWM1, HIGH);
	digitalWriteFast(REAR_PROP_PWM2, HIGH);
	digitalWriteFast(TOP_PROP_PWM, HIGH);
	digitalWriteFast(PIN_PF0, HIGH);
	delay(1);
	// Enable PWM output on motor GPIOs
	TCA0.SPLIT.CTRLB = TCA_SPLIT_HCMP0EN_bm | TCA_SPLIT_HCMP1EN_bm | TCA_SPLIT_LCMP2EN_bm | TCA_SPLIT_LCMP0EN_bm;

	topMotor(200);
	bottomMotor(200);
	
	//tailMotor(200, false);
	// TODO: modify tailmotor() to use brake mode instead of coast mode, as this fixes that motor speed issue.
	// These 3 lines do PWM with brake mode
	TCA0.SPLIT.CTRLB &= ~TCA_SPLIT_HCMP0EN_bm;
	digitalWriteFast(REAR_PROP_PWM1, HIGH);
	TCA0.SPLIT.HCMP1 = 50;

	SPI.swap(1);
	if (!radio.begin()) {
		Serial.println("Failed to start radio!");
		while (true) ;
	}
	radio.openWritingPipe(txAddress);
	radio.openReadingPipe(1, rxAddress);
	radio.setPALevel(RF24_PA_MAX);
	radio.startListening();
}

void setupMotorDrivers() {
	// Will set PWM frequency to 31.25 kHz.
	// Note: clock divider will be 2 and TCA0 is setup in 8-bit split mode
	analogWriteFrequency(32);

	// Set max (TOP) value back to 255, so we can get up to 99.6% duty cycle.
	// By default it is set to 254 which causes a bug: when we write 255 to the compare register, the PWM output completely dissapears because now a match and toggle never happens.
	TCA0.SPLIT.LPER = TCA0.SPLIT.HPER = 255;

	PORTMUX.TCAROUTEA = PORTMUX_TCA0_PORTF_gc; // Re-reoute TCA0 to PORTF
	// Set TCA0 compare value to zero for now so there is no output
	TCA0.SPLIT.LCMP0 = TCA0.SPLIT.LCMP1 = TCA0.SPLIT.LCMP2 = TCA0.SPLIT.HCMP0 = TCA0.SPLIT.HCMP1 = TCA0.SPLIT.HCMP2 = 0;

	// I accidentally wired the bottom motor to PD7, but that isnt connected to TCA0.
	// So actually we use TCA0 on PF0 as normal but then reroute through the event system peripheral back to PD7.

	// Route PF0 state onto event channel 5
	EVSYS.CHANNEL5 = EVSYS_GENERATOR_PORT1_PIN0_gc;
	// Connect event output D pin to channel 5
	EVSYS.USEREVOUTD = EVSYS_CHANNEL_CHANNEL5_gc;
	// Reroute event output D pin to PD7
	PORTMUX.EVSYSROUTEA |= PORTMUX_EVOUT3_bm;
}

float getVoltage() {
	return (float)(analogRead(BATT_DIVIDER) * 2) * 2.998f / 1023.0f;
}

/*void loop() {
	if (! bmp.performReading()) {
		Serial.println("Failed to perform reading :(");
		return;
	}
	Serial.print("Temperature = ");
	Serial.print(bmp.temperature);
	Serial.println(" *C");

	Serial.print("Pressure = ");
	Serial.print(bmp.pressure / 100.0);
	Serial.println(" hPa");

	Serial.print("Approx. Altitude = ");
	Serial.print(bmp.readAltitude(SEALEVELPRESSURE_HPA));
	Serial.println(" m");

	Serial.println();
	delay(2000);
}*/

unsigned long lastToggle = 0;
bool lastState = 0;

void loop() {
	if (radio.available()) {
    char buf[7];
    radio.read(buf, 7);
    Serial.println(buf);
	//radio.printPrettyDetails();
  }

  delay(10);
}

}

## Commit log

2024-12-21 Created project files
2024-12-26 Added basic connections for MCU
2024-12-26 Added basic connections for nrf24
2024-12-27 Basic connections for motor drivers
2024-12-30 Added basic connections for pressure sensor
2024-12-30 Basic connections for voltage regulator
2025-01-03 Finish motor driver circuits and move to subsheet
2025-01-04 Complete pressure sensor circuit
2025-01-10 Moved radio circuit to subsheet
2025-01-16 Created subsheet for power circuits
2025-01-16 Tidy net names & move BMP390 to subsheet
2025-01-16 Added UART and LED
2025-01-20 Added chassis LED connector
2025-01-21 Updated values to be in standard series
2025-01-23 Updated decoupling caps
2025-01-24 Updated footprints for the IC's
2025-01-24 Assigned footprints for connectors
2025-01-27 Misc small
    Remove ESD diode
    Add resistor to UPDI line
    Fix LED resistor
    Assign LED footprint
2025-01-27 Assigned footprint for mosfet
2025-01-28 Assigned footprint for crystal and button, fixed gitignore
2025-02-10 Added mounting holes and did board outline
    Also tried an initial layout with some components
2025-02-10 Assigned footprints for capacitors and inductors
2025-02-10 Corrected pin order on JST connectors
2025-02-11 Assigned resistor footprints
2025-02-12 Separated battery connector into 2 different
2025-02-12 Enlarge BMP390 pads and fix silkscreen
2025-02-27 Added separate LDO for NRF24
2025-02-27 Added power testpoints
2025-02-28 Update board outline and holes
2025-03-08 tryout more layout ideas
2025-03-09 Updated decoupling caps to match guidelines from Eric Bogatin
2025-03-11 Updated VRM capacitor values
2025-03-12 Setup board properties and design constraints
    Also added some default trace and via sizes
2025-03-13 Layout savepoint 1
2025-03-18 New layout idea, savepoint
    Me reckons this is the way to go. Only 1 motor bulk capacitor
2025-03-21 Layout update
2025-03-21 Reordered some MCU pin connections for nicer layout
2025-04-04 Pressure sensor now uses i2c
    Also rewired nrf24 to use the other SPI
2025-04-04 Added pin headers for external connections (PA6 and I2C)
2025-04-04 Reordered pins on programming connector for cleaner routing
2025-04-04 Shifted some things around
2025-04-05 Shifted radio components and testpoints around
2025-04-05 Fixed ERC errors
    Had to exclude warning for connecting ground to the bidirectional SA0 pin (pin 5) on the pressure sensor.
2025-04-09 Routed most of the radio traces
2025-04-09 Routed most pressure sensor traces
2025-04-10 Routed decoupling caps and PWM traces
2025-04-13 Fixed motor driver grounding
    Made new footprint with smaller thermal vias for less solder wicking.
    Added more vias in ground puddle.
2025-04-13 More signal trace routing and component placement
2025-04-14 Motor traces routing
2025-04-14 Routed crystal circuitry
2025-04-18 Better motor driver layout
    For the tail motor.
    I believe it to be better, who knows really.
    Although it does have longer PWM signal traces.
    Although the high current motor PWM traces are shorter which is good.
2025-04-18 Alternate motor driver layout
    For tail motor.
    Probably not going to use this one.
2025-04-19 MCU power and signal routing
2025-04-19 More power routing
2025-04-19 Finished off signal routing, also silkscreen fixes
2025-04-21 Created ground planes
2025-04-22 Fix via clearance and copper annuli
2025-04-25 thermal relief changes
2025-04-25 Added soldermask expansion on pressure sensor
2025-04-27 Fixed most DRC errors
    Had to modify some footprints
2025-05-02 Added 3d model for chassis led connector
2025-05-02 Added 3d model for reset pushbutton
2025-05-03 Experiment to see if 3rd motor driver is possible
2025-05-04 Finalise schematic to include 3rd motor driver
2025-05-04 Correct pin ordering for 3rd motor driver
2025-05-05 Almost done with new motor driver layout
2025-05-06 Finished routing for 3rd motor driver
2025-05-08 Increased trace width to handle battery charging current
2025-05-08 Fixed ERC error for multi-function pin on bmp390
2025-05-08 Add some soldermask expansion on motor drivers
2025-05-08 Fix pressure sensor 3d model
2025-05-09 Increased thermal relief spoke size on motor connections
2025-05-09 Increased B.Cu thermal pad size on motor drivers
2025-05-13 Fixed some unconnected tracks
2025-05-13 Fixed footprint DRC errors
2025-05-13 DRC exclusions for nrf24 GND pad
2025-05-29 Removed soldermask on back of motor driver thermal pads
2025-05-29 Add slight spacing between close components
2025-05-30 Added more gnd stitch vias
2025-05-30 Fixed fab layer
2025-05-30 Added part numbers for ~1/2 of components
2025-05-30 Made LED resistors bigger
    Physically, as in the footprint size
2025-06-03 Added MPN's for rest of components
2025-06-03 Added thermal pad connection to schematic
2025-06-06 Added silkscreen decoration
    Decided not to go with the pictures but I have still included the footprint files in the commit
2025-06-12 Updates to fields for PCBWay BOM generation
2025-06-14 More field changes for pcbway BOM
2025-06-22 Gerber and position files for pcbway
2025-07-26 Basic working code
2025-07-27 Update README.md
    Added PCBWay review
2025-07-28 Working voltage reading code
2025-08-01 started on pressure sense
2025-08-23 Working pressure sensor code
2025-09-02 Update README.md
    Added image of board
2025-10-04 Trying to get pwm generation
2025-10-04 Trying to fix pwm
2025-10-06 Fixing motor drivers
2025-10-18 Fixed motor issues
2025-10-19 Added radio test sketch
2025-10-19 Basic working radio code
2026-01-24 Implement initial controller and Task scheduling framework
2026-02-07 Added altimeter class and bosch library
2026-02-18 Basic radio communication components
2026-03-22 Initial app layout
2026-03-27 Added BLE framework to controller app
    Handles disconnect and reconnecting, and permissions
2026-03-28 Joysticks now send throttle to aerolink
2026-03-29 Aesthetic improvements for the controller app
2026-03-30 Added modal popup and linked this to permissions page
